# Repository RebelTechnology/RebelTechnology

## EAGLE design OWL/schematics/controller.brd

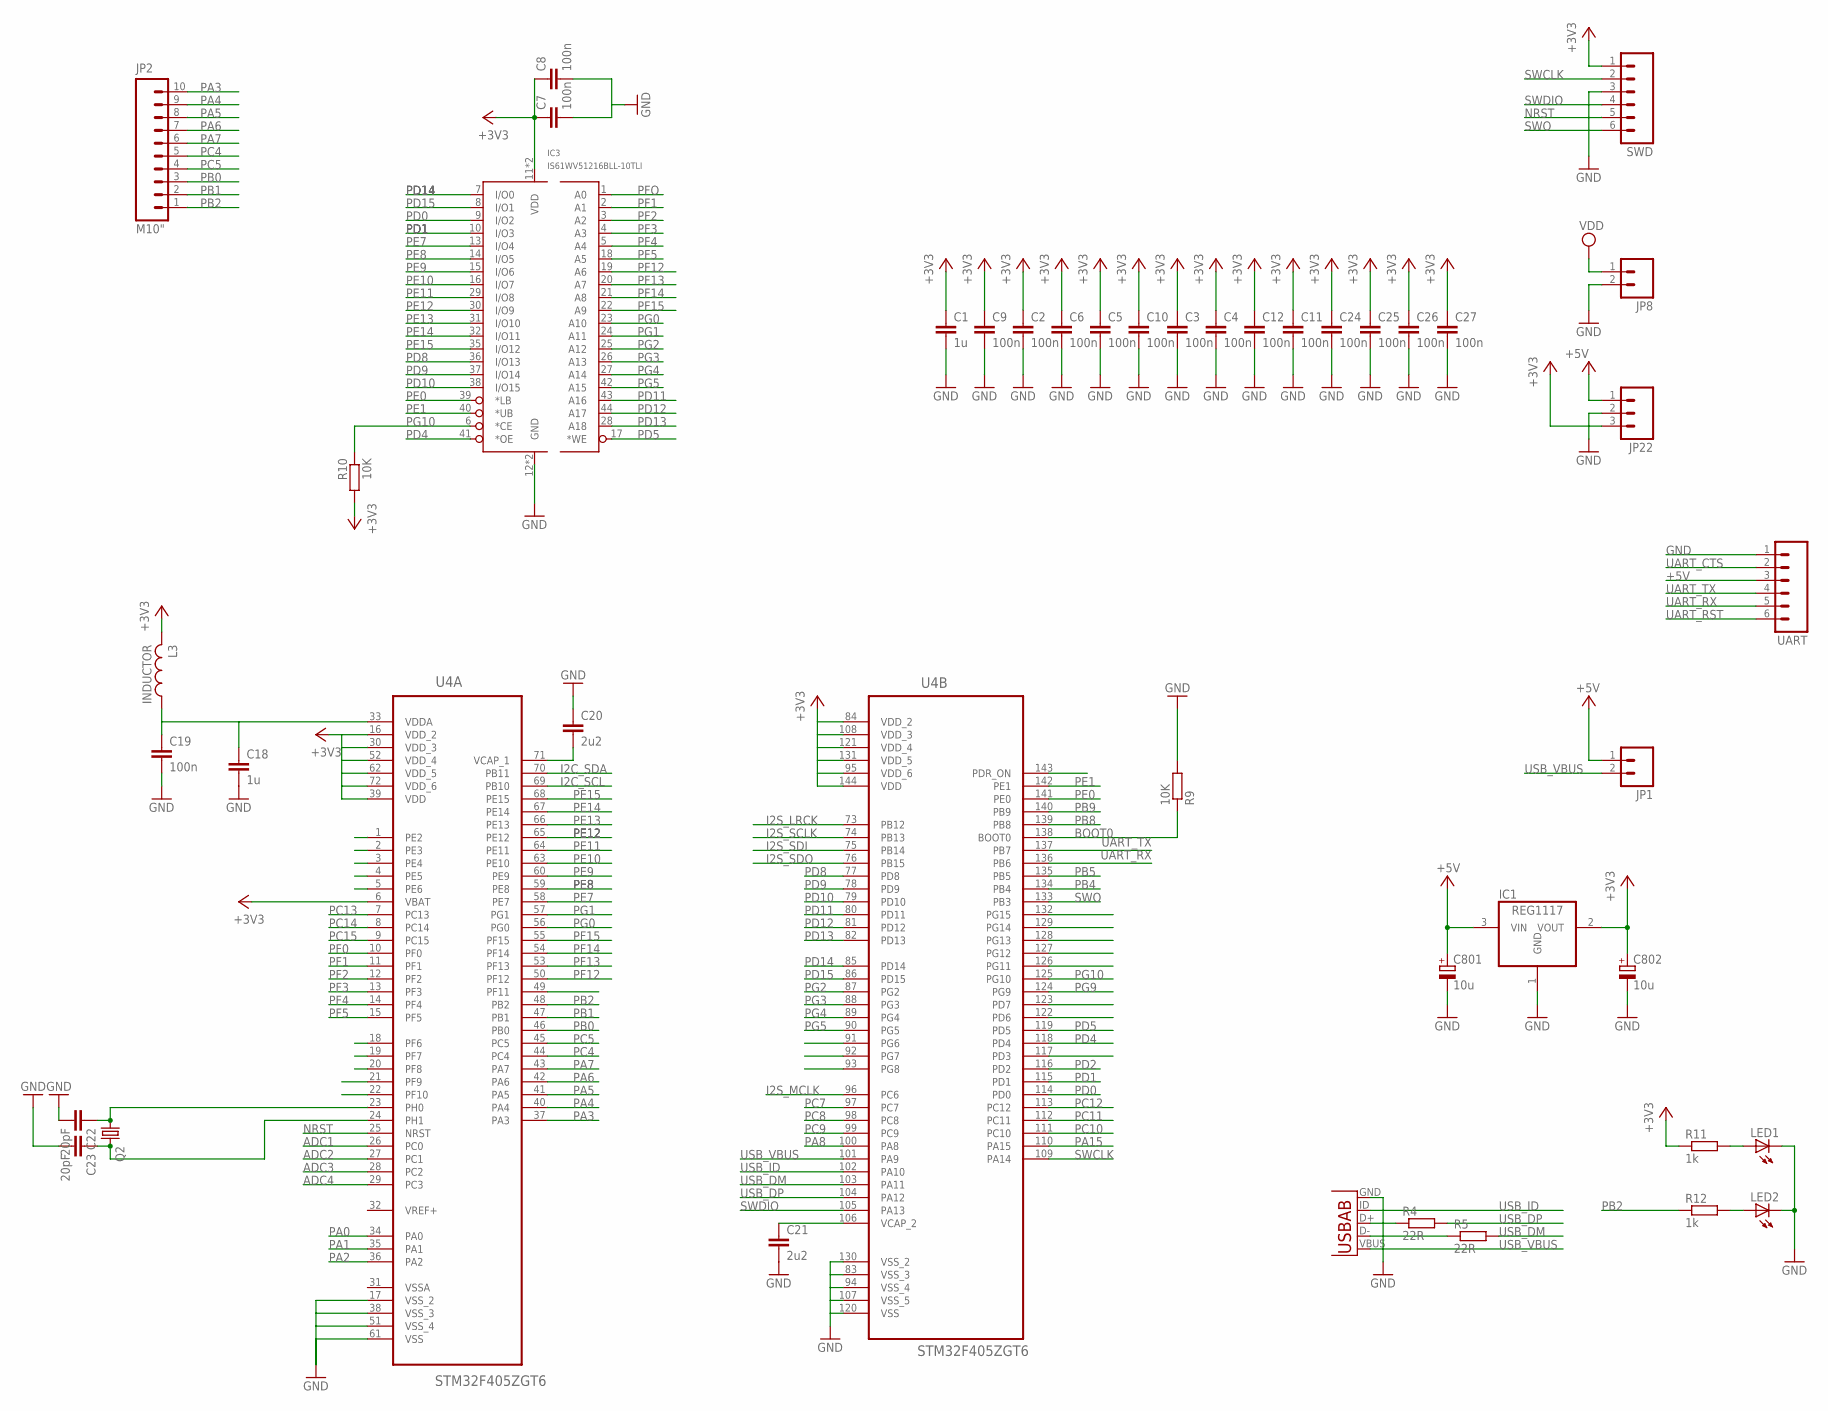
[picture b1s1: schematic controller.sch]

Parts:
C1, C18: 1u; C0603
C2, C3, C4, C5, C6, C7, C8, C9, C10, C11, C12, C19, C24, C25, C26, C27: 100n; C0603
C20, C21: 2u2; C0603
C22, C23: 20pF; C0603
C801, C802: 10u; PANASONIC_A
IC1: REG1117; SOT223
IC3: IS61WV51216BLL-10TLI; TSOP44-II
JP1, JP8: M02PTH; 1X02
JP2: M10"; 1X10
JP22: M03PTH; 1X03
L3: INDUCTOR; 0603
LED1, LED2: LED1206; LED-1206
Q2: CRYSTALHC49UP; HC49UP
R4, R5: 22R; R0603
R9, R10: 10K; R0603
R11, R12: 1k; R0603
SWD: M06SIP; 1X06
U3: USB-AB; USB-AB-MICRO-SMD
U4: STM32F405ZGT6; QFP50P2200X2200X160-144N
UART: M06SIP; 1X06

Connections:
+3V3: C1.1, C2.1, C3.1, C4.1, C5.1, C6.1, C7.1, C8.1, C9.1, C10.1, C11.1, C12.1, C24.1, C25.1, C26.1, C27.1, C802.+, IC1.2 (VOUT), IC3.11 (VDD), IC3.33 (VDD), JP22.3, L3.2, R10.2, R11.1, SWD.1, U4.6 (VBAT), U4.16 (VDD_2), U4.30 (VDD_3), U4.39 (VDD), U4.52 (VDD_4), U4.62 (VDD_5), U4.72 (VDD_6), U4.84 (VDD_2), U4.95 (VDD_6), U4.108 (VDD_3), U4.121 (VDD_4), U4.131 (VDD_5), U4.144 (VDD)
+5V: C801.+, IC1.3 (VIN), JP1.1, JP22.1, UART.3
ADC1: U4.26 (PC0)
ADC2: U4.27 (PC1)
ADC3: U4.28 (PC2)
ADC4: U4.29 (PC3)
BOOT0: R9.1, U4.138 (BOOT0)
GND: C1.2, C2.2, C3.2, C4.2, C5.2, C6.2, C7.2, C8.2, C9.2, C10.2, C11.2, C12.2, C18.2, C19.2, C20.1, C21.2, C22.2, C23.2, C24.2, C25.2, C26.2, C27.2, C801.-, C802.-, IC1.1 (GND), IC3.12 (GND), IC3.34 (GND), JP8.2, JP22.2, LED1.C, LED2.C, R9.2, SWD.3, U3.GND, U4.17 (VSS_2), U4.38 (VSS_3), U4.51 (VSS_4), U4.61 (VSS), U4.83 (VSS_3), U4.94 (VSS_4), U4.107 (VSS_5), U4.120 (VSS), U4.130 (VSS_2), UART.1
I2C_SCL: U4.69 (PB10)
I2C_SDA: U4.70 (PB11)
I2S_LRCK: U4.73 (PB12)
I2S_MCLK: U4.96 (PC6)
I2S_SCLK: U4.74 (PB13)
I2S_SDI: U4.75 (PB14)
I2S_SDO: U4.76 (PB15)
unnamed: LED1.A, R11.2
unnamed: LED2.A, R12.2
unnamed: C21.1, U4.106 (VCAP_2)
unnamed: R4.1, U3.D+
unnamed: R5.1, U3.D-
unnamed: C23.1, Q2.2, U4.24 (PH1)
unnamed: C22.1, Q2.1, U4.23 (PH0)
unnamed: C20.2, U4.71 (VCAP_1)
NRST: SWD.5, U4.25 (NRST)
PA0: U4.34 (PA0)
PA1: U4.35 (PA1)
PA2: U4.36 (PA2)
PA3: JP2.10, U4.37 (PA3)
PA4: JP2.9, U4.40 (PA4)
PA5: JP2.8, U4.41 (PA5)
PA6: JP2.7, U4.42 (PA6)
PA7: JP2.6, U4.43 (PA7)
PA8: U4.100 (PA8)
PA15: U4.110 (PA15)
PB0: JP2.3, U4.46 (PB0)
PB1: JP2.2, U4.47 (PB1)
PB2: JP2.1, R12.1, U4.48 (PB2)
PB4: U4.134 (PB4)
PB5: U4.135 (PB5)
PB8: U4.139 (PB8)
PB9: U4.140 (PB9)
PC4: JP2.5, U4.44 (PC4)
PC5: JP2.4, U4.45 (PC5)
PC7: U4.97 (PC7)
PC8: U4.98 (PC8)
PC9: U4.99 (PC9)
PC10: U4.111 (PC10)
PC11: U4.112 (PC11)
PC12: U4.113 (PC12)
PC13: U4.7 (PC13)
PC14: U4.8 (PC14)
PC15: U4.9 (PC15)
PD0: IC3.9 (I/O2), U4.114 (PD0)
PD1: IC3.10 (I/O3), U4.115 (PD1)
PD2: U4.116 (PD2)
PD4: IC3.41 (*OE), U4.118 (PD4)
PD5: IC3.17 (*WE), U4.119 (PD5)
PD8: IC3.36 (I/O13), U4.77 (PD8)
PD9: IC3.37 (I/O14), U4.78 (PD9)
PD10: IC3.38 (I/O15), U4.79 (PD10)
PD11: IC3.43 (A16), U4.80 (PD11)
PD12: IC3.44 (A17), U4.81 (PD12)
PD13: IC3.28 (A18), U4.82 (PD13)
PD14: IC3.7 (I/O0), U4.85 (PD14)
PD15: IC3.8 (I/O1), U4.86 (PD15)
PE0: IC3.39 (*LB), U4.141 (PE0)
PE1: IC3.40 (*UB), U4.142 (PE1)
PE7: IC3.13 (I/O4), U4.58 (PE7)
PE8: IC3.14 (I/O5), U4.59 (PE8)
PE9: IC3.15 (I/O6), U4.60 (PE9)
PE10: IC3.16 (I/O7), U4.63 (PE10)
PE11: IC3.29 (I/O8), U4.64 (PE11)
PE12: IC3.30 (I/O9), U4.65 (PE12)
PE13: IC3.31 (I/O10), U4.66 (PE13)
PE14: IC3.32 (I/O11), U4.67 (PE14)
PE15: IC3.35 (I/O12), U4.68 (PE15)
PF0: U4.10 (PF0)
PF1: IC3.2 (A1), U4.11 (PF1)
PF2: IC3.3 (A2), U4.12 (PF2)
PF3: IC3.4 (A3), U4.13 (PF3)
PF4: IC3.5 (A4), U4.14 (PF4)
PF5: IC3.18 (A5), U4.15 (PF5)
PF9: U4.20 (PF8)
PF12: IC3.19 (A6), U4.50 (PF12)
PF13: IC3.20 (A7), U4.53 (PF13)
PF14: IC3.21 (A8), U4.54 (PF14)
PF15: IC3.22 (A9), U4.55 (PF15)
PFO: IC3.1 (A0)
PG0: IC3.23 (A10), U4.56 (PG0)
PG1: IC3.24 (A11), U4.57 (PG1)
PG2: IC3.25 (A12), U4.87 (PG2)
PG3: IC3.26 (A13), U4.88 (PG3)
PG4: IC3.27 (A14), U4.89 (PG4)
PG5: IC3.42 (A15), U4.90 (PG5)
PG9: U4.124 (PG9)
PG10: IC3.6 (*CE), R10.1, U4.125 (PG10)
SWCLK: SWD.2, U4.109 (PA14)
SWDIO: SWD.4, U4.105 (PA13)
SWO: SWD.6, U4.133 (PB3)
UART_CTS: UART.2
UART_RST: UART.6
UART_RX: U4.136 (PB6), UART.5
UART_TX: U4.137 (PB7), UART.4
USB_DM: R5.2, U4.103 (PA11)
USB_DP: R4.2, U4.104 (PA12)
USB_ID: U3.ID (USBID), U4.102 (PA10)
USB_VBUS: JP1.2, U3.VBUS, U4.101 (PA9)
VDD: JP8.1
VDDA: C18.1, C19.1, L3.1, U4.33 (VDDA)
VSSA: U4.31 (VSSA)

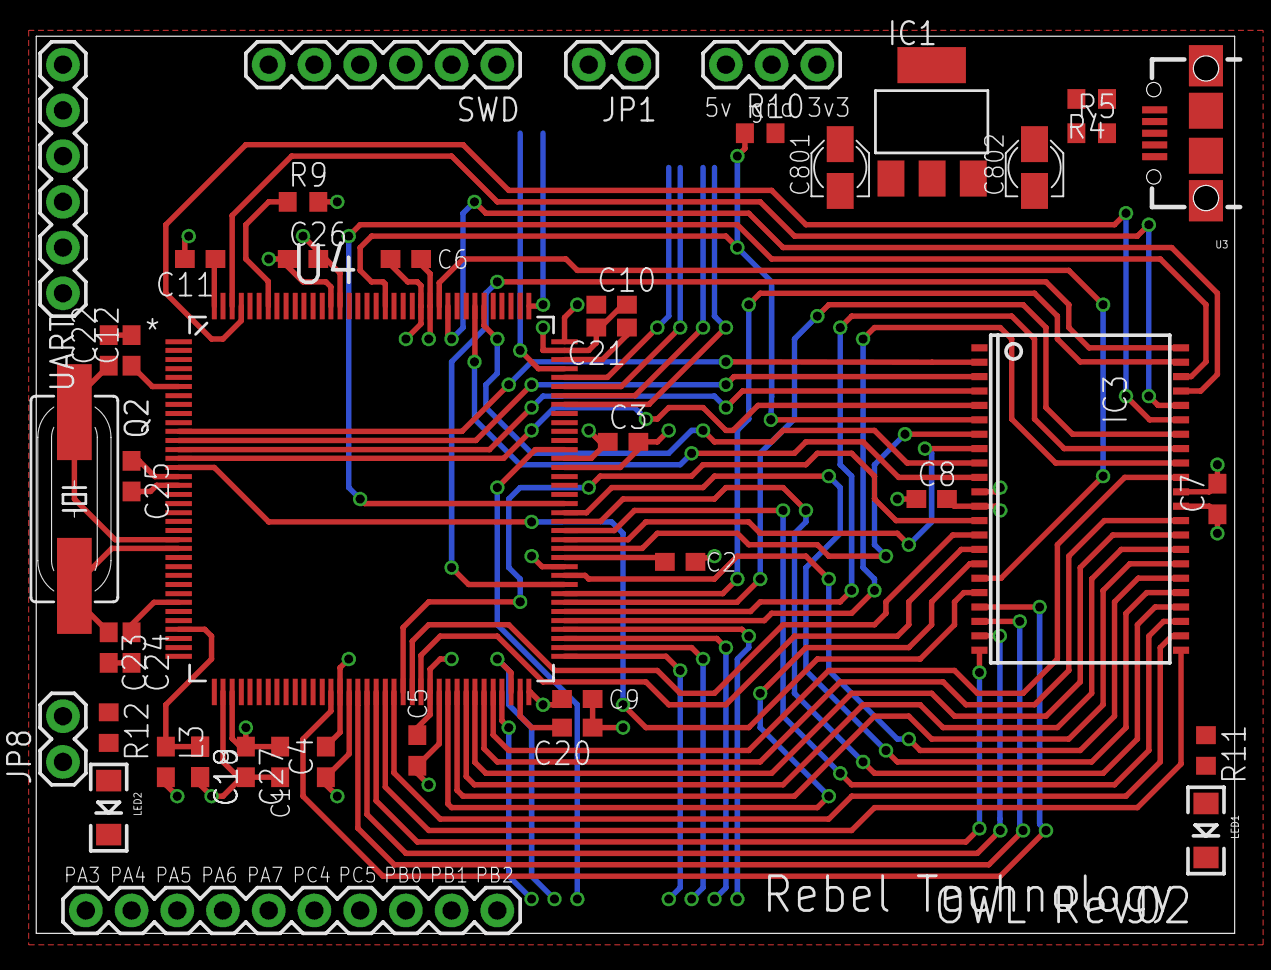
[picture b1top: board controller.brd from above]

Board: 2 copper layers, 66.6 x 49.8 mm, 44 parts (0 on the bottom side), 72 nets.

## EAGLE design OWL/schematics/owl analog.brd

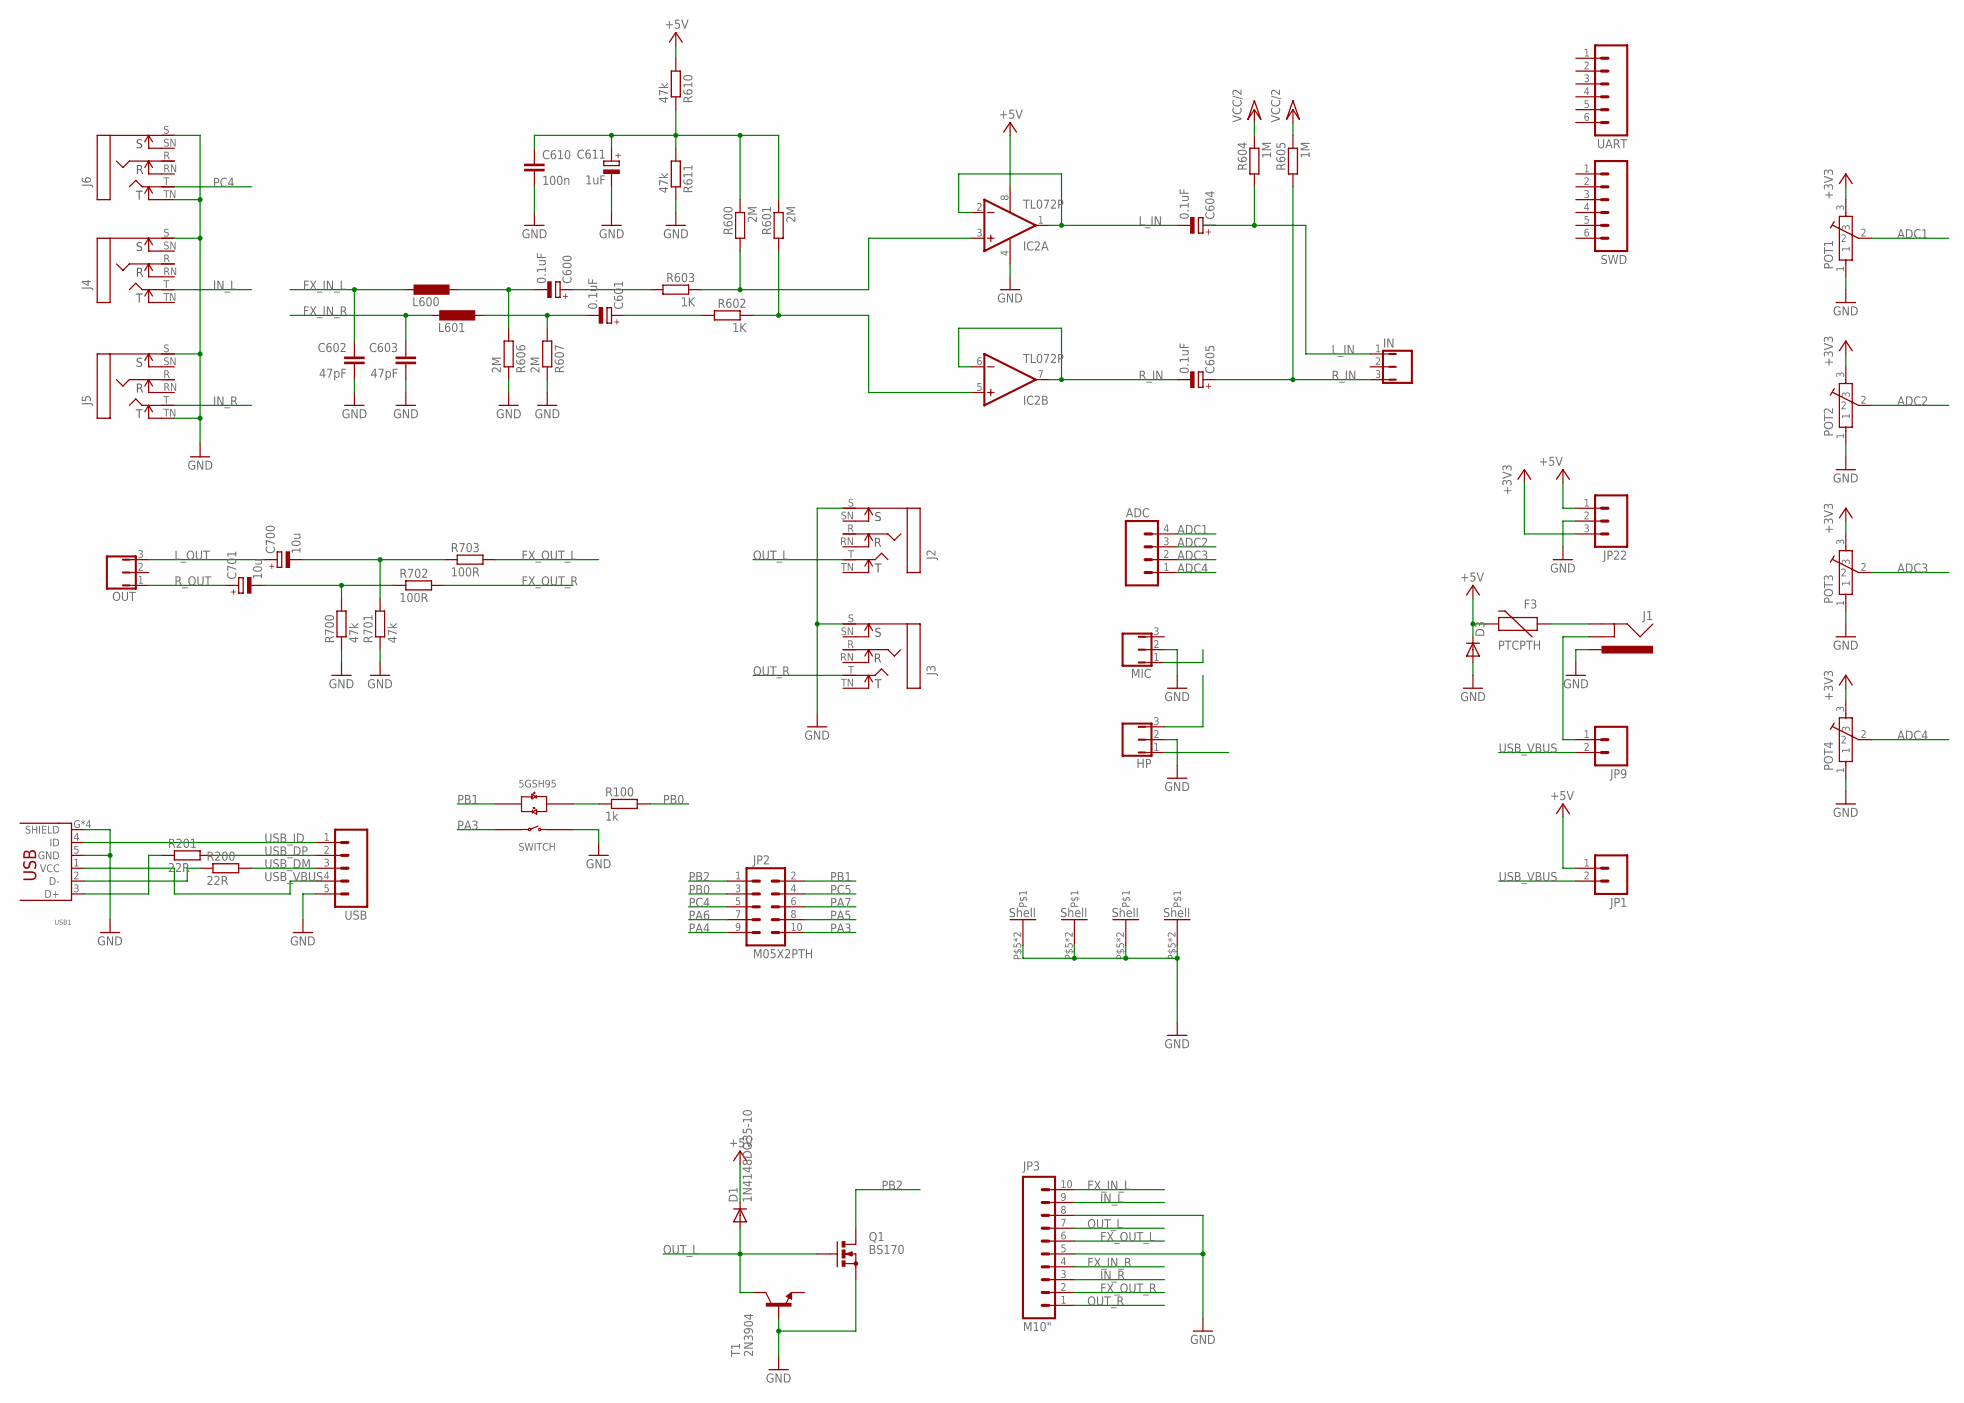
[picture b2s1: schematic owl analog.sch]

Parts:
ADC: M04PTH; 1X04
C600, C601, C604, C605: 0.1uF; E2,5-7
C602, C603: 47pF; C050-025X075
C610: 100n; C050-025X075
C611: 1uF; E2,5-7
C700, C701: 10u; E2,5-7
D1: 1N4148DO35-10; DO35-10
D3: DIODE1N4001; DIODE-1N4001
F3: PTCPTH; PTC
HP: JMP/3P/SIP
IC2: TL072P; DIL08
IN: JMP/3P/SIP
J1: POWER_JACKPTH; POWER_JACK_PTH
J2, J3, J4, J5, J6: NEUTRIK_NMJ6HCD2; NMJ6HCD2
JP1, JP9: M02PTH; 1X02
JP2: M05X2PTH; AVR_ICSP
JP3: M10"; 1X10
JP22: M03PTH; 1X03
L600, L601: L-EUIRF-1; IRF-1
MIC: JMP/3P/SIP
OUT: JMP/3P/SIP
POT1, POT2, POT3, POT4: POT-ALPS-RK09L1140
Q1: BS170; SOT54E
R100: 1k; 0204/7
R200, R201: 22R; 0204/7
R600, R601, R606, R607: 2M; 0204/7
R602, R603: 1K; 0204/7
R604, R605: 1M; 0204/7
R610, R611, R700, R701: 47k; 0204/7
R702, R703: 100R; 0204/7
SWD: M06SIP; 1X06
T1: 2N3904; TO92
U$1: 5GTH9
UART: M06SIP; 1X06
USB: M05PTH; 1X05
USB1: USB_HRS_ZX62-B-5PA(11)MICRO.B-; HRS_ZX62D-AB-5P8_USB

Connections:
+3V3: JP22.3, POT1.3, POT2.3, POT3.3, POT4.3
+5V: D1.C, D3.C, F3.P$2 (2), IC2.8 (V+), JP1.1, JP22.1, R610.2
ADC1: ADC.4, POT1.2
ADC2: ADC.3, POT2.2
ADC3: ADC.2, POT3.2
ADC4: ADC.1, POT4.2
FX_IN_L: C602.1, JP3.10, L600.2
FX_IN_R: C603.1, JP3.4, L601.2
FX_OUT_L: JP3.6, R703.2
FX_OUT_R: JP3.2, R702.2
GND: C602.2, C603.2, C610.2, C611.-, D3.A, HP.2, IC2.4 (V-), J1.PWR, J2.S, J3.S, J4.S, J5.S, J5.TN, J6.S, J6.TN, JP3.5, JP3.8, JP22.2, MIC.2, POT1.1, POT1.P$5, POT1.P$6, POT2.1, POT2.P$5, POT2.P$6, POT3.1, POT3.P$5, POT3.P$6, POT4.1, POT4.P$5, POT4.P$6, Q1.S, R606.1, R607.1, R611.1, R700.1, R701.1, T1.2 (B), U$1.+3 (3+), USB.5, USB1.5 (GND), USB1.G (SHIELD), USB1.G2 (SHIELD), USB1.G3 (SHIELD), USB1.G4 (SHIELD)
IN_L: J4.T, JP3.9
IN_R: J5.T, JP3.3
L_IN: C604.-, IC2.1 (OUT), IC2.2 (-IN), IN.1, R604.2
L_OUT: C700.+, OUT.3
unnamed: R201.1, USB1.3 (D+)
unnamed: C600.-, L600.1, R606.2
unnamed: C601.-, L601.1, R607.2
unnamed: F3.P$1 (1), J1.GND
unnamed: J1.GNDBREAK, JP9.1
unnamed: R200.1, USB1.2 (D-)
unnamed: C600.+, R603.2
unnamed: C601.+, R602.2
unnamed: R100.1, U$1.1
unnamed: C610.1, C611.+, R600.1, R601.1, R610.1, R611.2
unnamed: C701.-, R700.2, R702.1
unnamed: C700.-, R701.2, R703.1
unnamed: IC2.3 (+IN), R600.2, R603.1
unnamed: IC2.5 (+IN), R601.2, R602.1
OUT_L: D1.A, J2.T, JP3.7, Q1.G, T1.1 (C)
OUT_R: J3.T, JP3.1
PA3: JP2.10, U$1.4
PA4: JP2.9
PA5: JP2.8
PA6: JP2.7
PA7: JP2.6
PB0: JP2.3, R100.2
PB1: JP2.2, U$1.-2 (2)
PB2: JP2.1, Q1.D
PC4: J6.T, JP2.5
PC5: JP2.4
R_IN: C605.+, C605.-, IC2.6 (-IN), IC2.7 (OUT), IN.3, R605.2
R_OUT: C701.+, OUT.1
USB_DM: R200.2, USB.3
USB_DP: R201.2, USB.2
USB_ID: USB.1, USB1.4 (ID)
USB_VBUS: JP1.2, JP9.2, USB.4, USB1.1 (VCC)
VCC/2: R604.1, R605.1

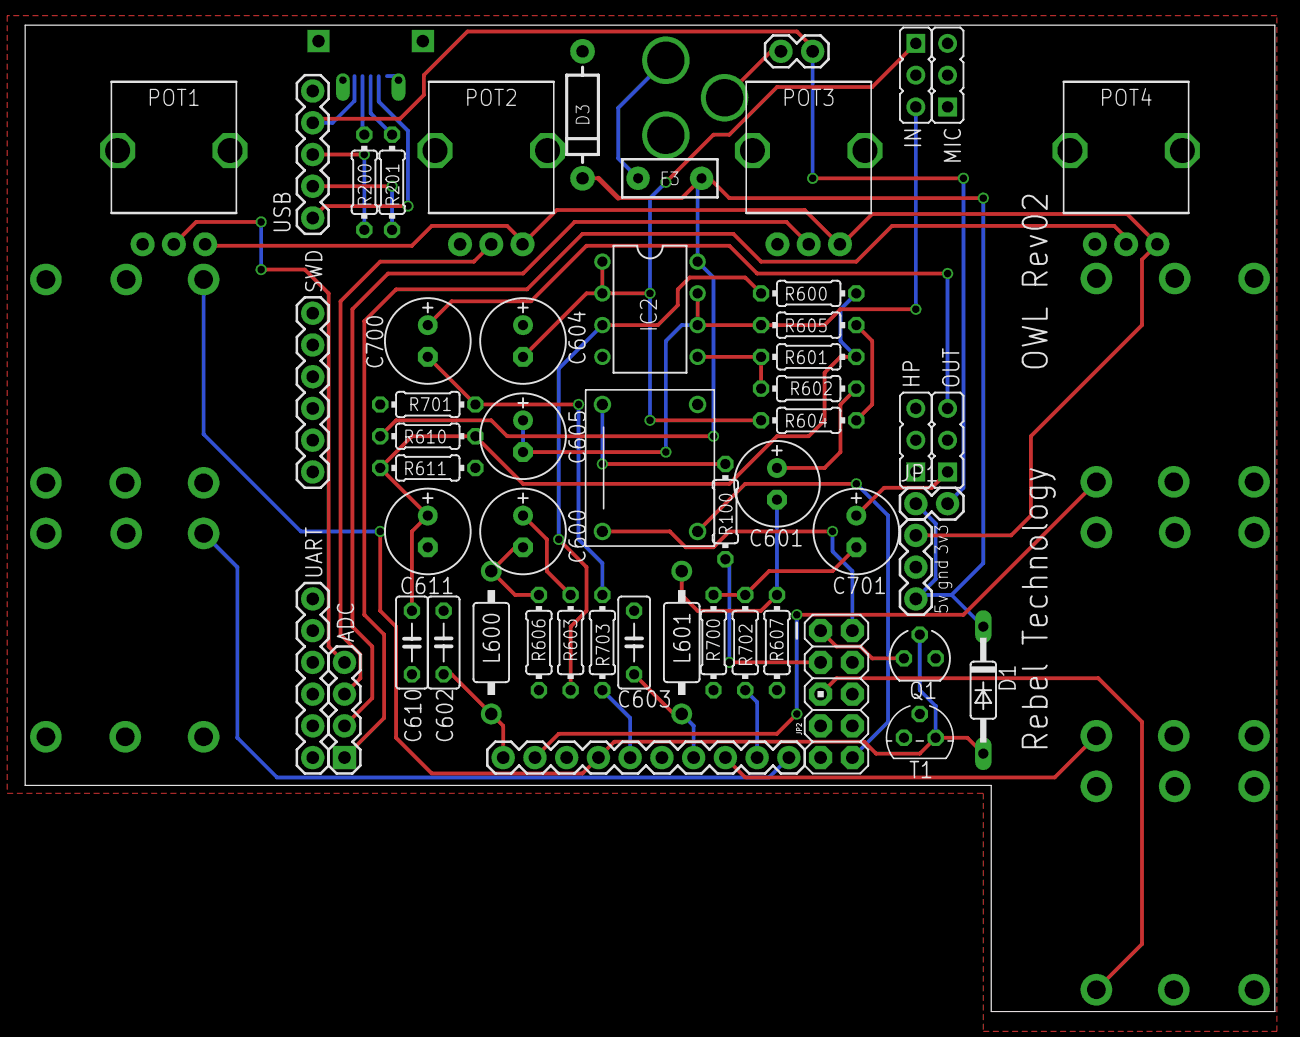
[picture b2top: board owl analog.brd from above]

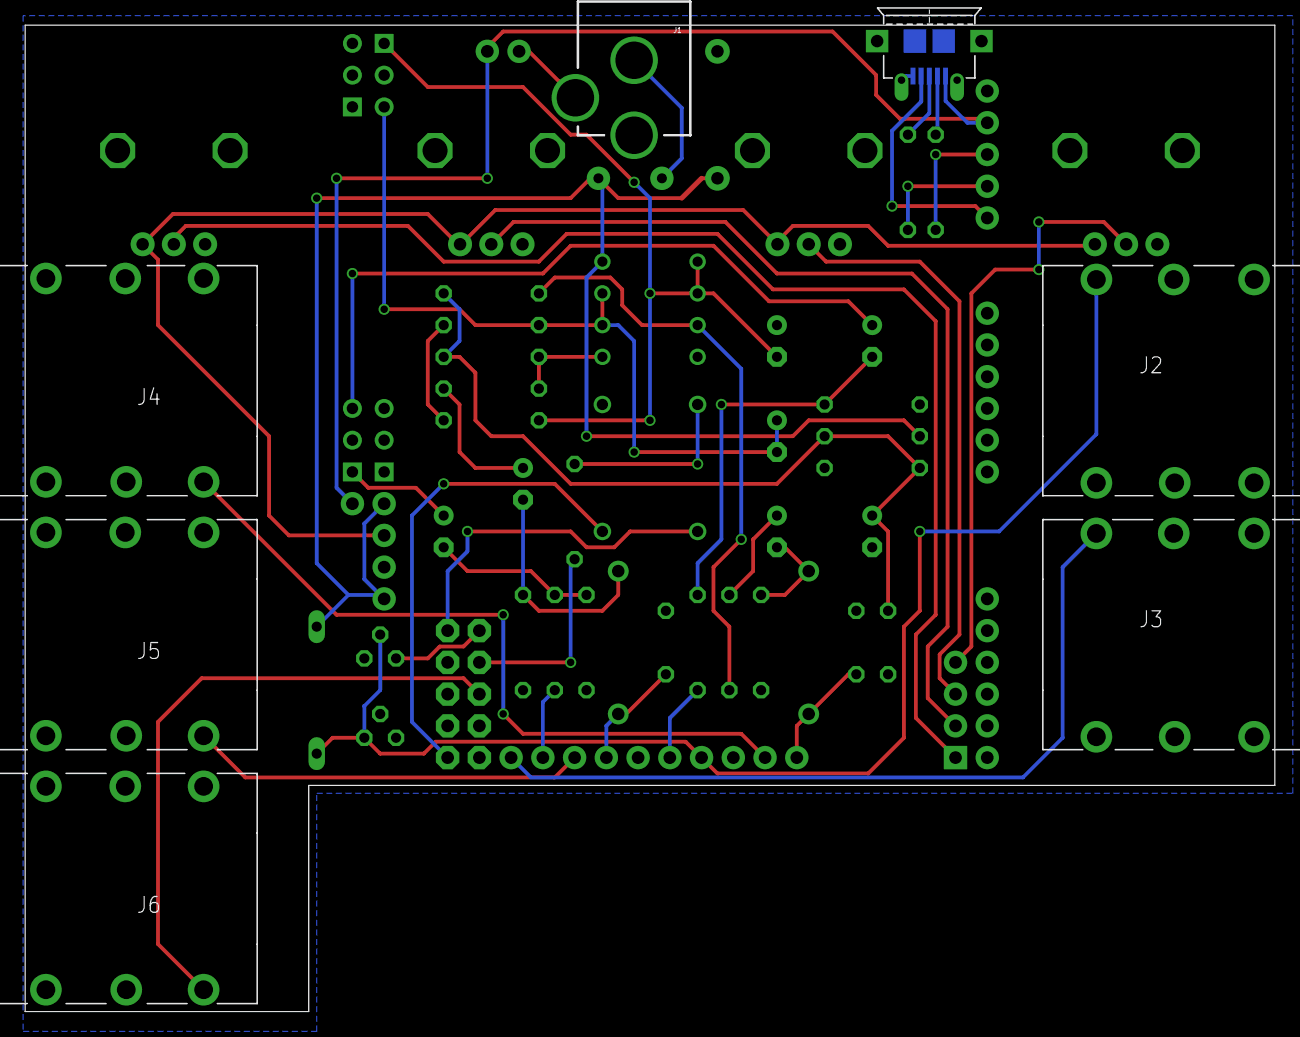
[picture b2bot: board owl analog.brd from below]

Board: 2 copper layers, 100.0 x 78.9 mm, 60 parts (7 on the bottom side), 43 nets.

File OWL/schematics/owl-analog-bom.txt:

Partlist

Exported from owl-analog.sch at 23/08/2013 17:49

EAGLE Version 6.4.0 Copyright (c) 1988-2013 CadSoft

Assembly variant: 

Part     Value              Device                         Package              Library                 Sheet

ADC                         M04PTH                         1X04                 SparkFun                1
C600     0.1uF              CPOL-EUE2.5-7                  E2,5-7               rcl                     1
C601     0.1uF              CPOL-EUE2.5-7                  E2,5-7               rcl                     1
C602     47pF               C-EU050-025X075                C050-025X075         rcl                     1
C603     47pF               C-EU050-025X075                C050-025X075         rcl                     1
C604     0.1uF              CPOL-EUE2.5-7                  E2,5-7               rcl                     1
C605     0.1uF              CPOL-EUE2.5-7                  E2,5-7               rcl                     1
C610     100n               C-EU050-025X075                C050-025X075         rcl                     1
C611     1uF                CPOL-EUE2.5-7                  E2,5-7               rcl                     1
C700     10u                CPOL-EUE2.5-7                  E2,5-7               rcl                     1
C701     10u                CPOL-EUE2.5-7                  E2,5-7               rcl                     1
D1       1N4148DO35-10      1N4148DO35-10                  DO35-10              diode                   1
D3                          DIODE1N4001                    DIODE-1N4001         Rebel                   1
F3       PTCPTH             PTCPTH                         PTC                  Rebel                   1
HP                          JMP/3P/SIP                     JMP/3P/SIP           audioint                1
IC2      TL072P             TL072P                         DIL08                linear                  1
IN                          JMP/3P/SIP                     JMP/3P/SIP           audioint                1
J1                          POWER_JACKPTH                  POWER_JACK_PTH       SparkFun                1
J2       NEUTRIK_NMJ6HCD2   NEUTRIK_NMJ6HCD2               NMJ6HCD2             neutrik_jacks           1
J3       NEUTRIK_NMJ6HCD2   NEUTRIK_NMJ6HCD2               NMJ6HCD2             neutrik_jacks           1
J4       NEUTRIK_NMJ6HCD2   NEUTRIK_NMJ6HCD2               NMJ6HCD2             neutrik_jacks           1
J5       NEUTRIK_NMJ6HCD2   NEUTRIK_NMJ6HCD2               NMJ6HCD2             neutrik_jacks           1
J6       NEUTRIK_NMJ6HCD2   NEUTRIK_NMJ6HCD2               NMJ6HCD2             neutrik_jacks           1
JP1                         M02PTH                         1X02                 SparkFun                1
JP2      M05X2PTH           M05X2PTH                       AVR_ICSP             SparkFun                1
JP3      M10"               M10"                           1X10                 SparkFun                1
JP9                         M02PTH                         1X02                 SparkFun                1
JP22                        M03PTH                         1X03                 SparkFun                1
L600                        L-EUIRF-1                      IRF-1                rcl                     1
L601                        L-EUIRF-1                      IRF-1                rcl                     1
MIC                         JMP/3P/SIP                     JMP/3P/SIP           audioint                1
OUT                         JMP/3P/SIP                     JMP/3P/SIP           audioint                1
POT1     POT-ALPS-RK09L1140 POT-ALPS-RK09L1140             POT-ALPS-RK09L1140   Rebel                   1
POT2     POT-ALPS-RK09L1140 POT-ALPS-RK09L1140             POT-ALPS-RK09L1140   Rebel                   1
POT3     POT-ALPS-RK09L1140 POT-ALPS-RK09L1140             POT-ALPS-RK09L1140   Rebel                   1
POT4     POT-ALPS-RK09L1140 POT-ALPS-RK09L1140             POT-ALPS-RK09L1140   Rebel                   1
Q1       BS170              BS170                          SOT54E               transistor-small-signal 1
R100     1k                 R-EU_0204/7                    0204/7               Rebel                   1
R200     22R                R-EU_0204/7                    0204/7               Rebel                   1
R201     22R                R-EU_0204/7                    0204/7               Rebel                   1
R600     2M                 R-EU_0204/7                    0204/7               Rebel                   1
R601     2M                 R-EU_0204/7                    0204/7               Rebel                   1
R602     1K                 R-EU_0204/7                    0204/7               Rebel                   1
R603     1K                 R-EU_0204/7                    0204/7               Rebel                   1
R604     1M                 R-EU_0204/7                    0204/7               Rebel                   1
R605     1M                 R-EU_0204/7                    0204/7               Rebel                   1
R606     2M                 R-EU_0204/7                    0204/7               Rebel                   1
R607     2M                 R-EU_0204/7                    0204/7               Rebel                   1
R610     47k                R-EU_0204/7                    0204/7               Rebel                   1
R611     47k                R-EU_0204/7                    0204/7               Rebel                   1
R700     47k                R-EU_0204/7                    0204/7               Rebel                   1
R701     47k                R-EU_0204/7                    0204/7               Rebel                   1
R702     100R               R-EU_0204/7                    0204/7               Rebel                   1
R703     100R               R-EU_0204/7                    0204/7               Rebel                   1
SWD                         M06SIP                         1X06                 SparkFun                1
T1       2N3904             2N3904                         TO92                 transistor              1
U$1      5GTH9              5GTH9                          5GTH9                SWITCH-5GTH9            1
UART                        M06SIP                         1X06                 SparkFun                1
USB                         M05PTH                         1X05                 SparkFun                1
USB1                        USB_HRS_ZX62-B-5PA(11)MICRO.B- HRS_ZX62D-AB-5P8_USB USB_connector           1

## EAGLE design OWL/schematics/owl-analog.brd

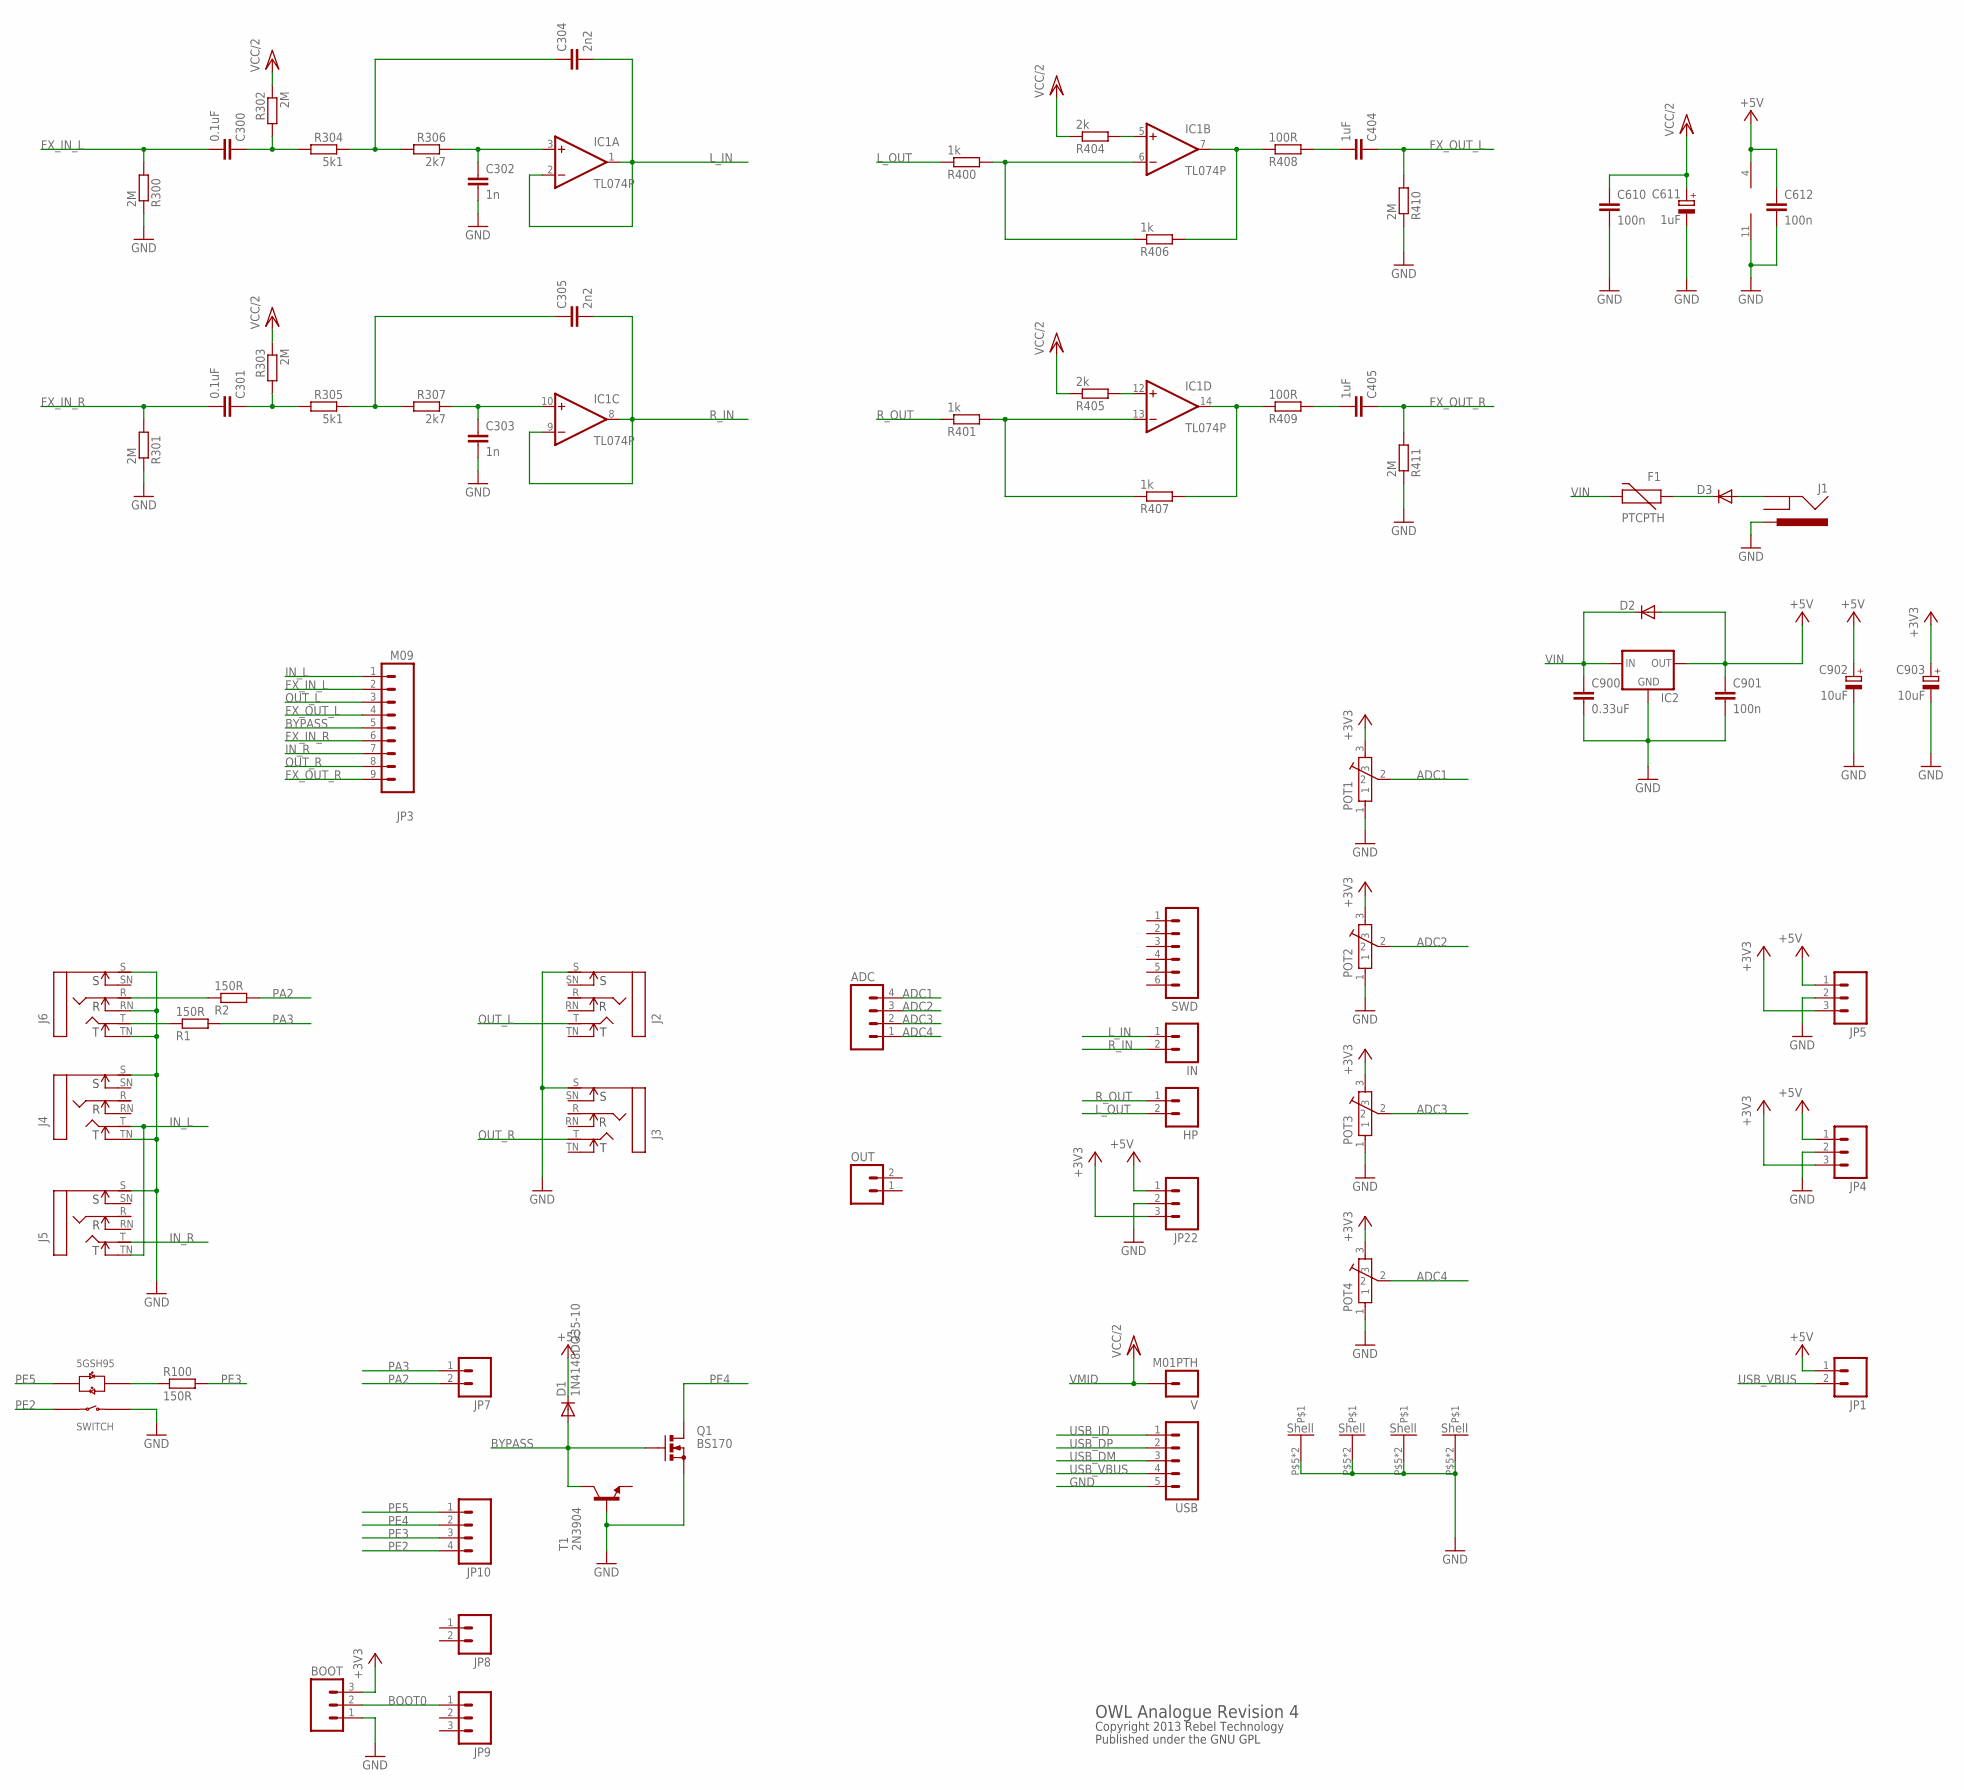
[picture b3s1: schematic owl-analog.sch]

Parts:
ADC: M04PTH; 1X04
BOOT: M03PTH; 1X03
C300, C301: 0.1uF; C5B3.5
C302, C303: 1n; C5B2.5
C304: 2n2; C5B2.5
C305: 2n2; C050-025X075
C404, C405: 1uF; C5B5
C610, C612, C901: 100n; C050-025X075
C611: 1uF; E2,5-7
C900: 0.33uF; C050-025X075
C902, C903: 10uF; E2,5-7
D1: 1N4148DO35-10; DO35-10
D2, D3: DIODE1N4001; DIODE-1N4001
F1: PTCPTH; PTC
HP: M02PTH; 1X02
IC1: TL074P; DIL14
IC2: V_REG_78XX-TO-220; TO-220-ALT
IN: M02PTH; 1X02
J1: POWER_JACKPTH; POWER_JACK_PTH
J2, J3, J4, J5, J6: NEUTRIK_NMJ6HCD2; NMJ6HCD2
JP1, JP7, JP8: M02PTH; 1X02
JP3: M09; 1X09
JP4, JP5, JP9, JP22: M03PTH; 1X03
JP10: M04PTH; 1X04
OUT: M02PTH; 1X02
POT1, POT2, POT3, POT4: POT-ALPS-RK09L1140
Q1: BS170; SOT54E
R1, R2, R100: 150R; 0204/7
R300, R301, R302, R303, R410, R411: 2M; 0204/7
R304, R305: 5k1; 0204/7
R306, R307: 2k7; 0204/7
R400, R401, R406, R407: 1k; 0204/7
R404, R405: 2k; 0204/7
R408, R409: 100R; 0204/7
SWD: M06SIP; 1X06
T1: 2N3904; TO92
U$1: 5GTH9
USB: M05PTH; 1X05
V: M01PTH; 1X01

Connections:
+3V3: BOOT.3, C903.+, JP4.3, JP5.3, JP22.3, POT1.3, POT2.3, POT3.3, POT4.3
+5V: C612.1, C901.1, C902.+, D1.C, D2.A, IC1.4 (V+), IC2.OUT, JP1.1, JP4.1, JP5.1, JP22.1
+5V/1: IC1.5 (+IN), R404.2
ADC1: ADC.4, POT1.2
ADC2: ADC.3, POT2.2
ADC3: ADC.2, POT3.2
ADC4: ADC.1, POT4.2
BOOT0: BOOT.2, JP9.1
BYPASS: D1.A, JP3.5, Q1.G, T1.1 (C)
FX_IN_L: C300.2, JP3.2, R300.2
FX_IN_R: C301.2, JP3.6, R301.2
FX_OUT_L: C404.1, JP3.4, R410.2
FX_OUT_R: C405.1, JP3.9, R411.2
GND: BOOT.1, C302.2, C303.2, C610.2, C611.-, C612.2, C900.2, C901.2, C902.-, C903.-, IC1.11 (V-), IC2.GND, J1.PWR, J2.S, J3.S, J4.S, J4.TN, J5.S, J6.RN, J6.S, J6.TN, JP4.2, JP5.2, JP22.2, POT1.1, POT1.P$5, POT1.P$6, POT2.1, POT2.P$5, POT2.P$6, POT3.1, POT3.P$5, POT3.P$6, POT4.1, POT4.P$5, POT4.P$6, Q1.S, R300.1, R301.1, R410.1, R411.1, T1.2 (B), U$1.1 (SWITCH_B), USB.5
IN_L: J4.T, J5.TN, JP3.1
IN_R: J5.T, JP3.7
L_IN: C304.2, IC1.1 (OUT), IC1.2 (-IN), IN.1
L_OUT: HP.2, R400.1
unnamed: D3.A, J1.GND
unnamed: IC1.12 (+IN), R405.2
unnamed: D3.C, F1.P$1 (1)
unnamed: R100.1, U$1.+3 (LED_R+)
unnamed: J6.R, R2.1
unnamed: J6.T, R1.1
unnamed: C300.1, R302.2, R304.2
unnamed: C405.2, R409.2
unnamed: C301.1, R303.2, R305.2
unnamed: C303.1, IC1.10 (+IN), R307.1
unnamed: C304.1, R304.1, R306.2
unnamed: C305.1, R305.1, R307.2
unnamed: C404.2, R408.2
unnamed: C302.1, IC1.3 (+IN), R306.1
unnamed: IC1.7 (OUT), R406.2, R408.1
unnamed: IC1.14 (OUT), R407.2, R409.1
unnamed: IC1.6 (-IN), R400.2, R406.1
unnamed: IC1.13 (-IN), R401.2, R407.1
OUT_L: J2.T, JP3.3
OUT_R: J3.T, JP3.8
PA2: JP7.2, R2.2
PA3: JP7.1, R1.2
PE2: JP10.4, U$1.4 (SWITCH_A)
PE3: JP10.3, R100.2
PE4: JP10.2, Q1.D
PE5: JP10.1, U$1.-2 (LED_G+)
R_IN: C305.2, IC1.8 (OUT), IC1.9 (-IN), IN.2
R_OUT: HP.1, R401.1
USB_DM: USB.3
USB_DP: USB.2
USB_ID: USB.1
USB_VBUS: JP1.2, USB.4
VIN: C900.1, D2.C, F1.P$2 (2), IC2.IN
VMID: C610.1, C611.+, R302.1, R303.1, R404.1, R405.1, V.1

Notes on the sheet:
Copyright 2013 Rebel Technology
Published under the GNU GPL
OWL Analogue Revision 4

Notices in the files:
parts and their libraries:
SparkFun: Licensing: CC v3.0 Share-Alike You are welcome to use this library for commercial purposes.
